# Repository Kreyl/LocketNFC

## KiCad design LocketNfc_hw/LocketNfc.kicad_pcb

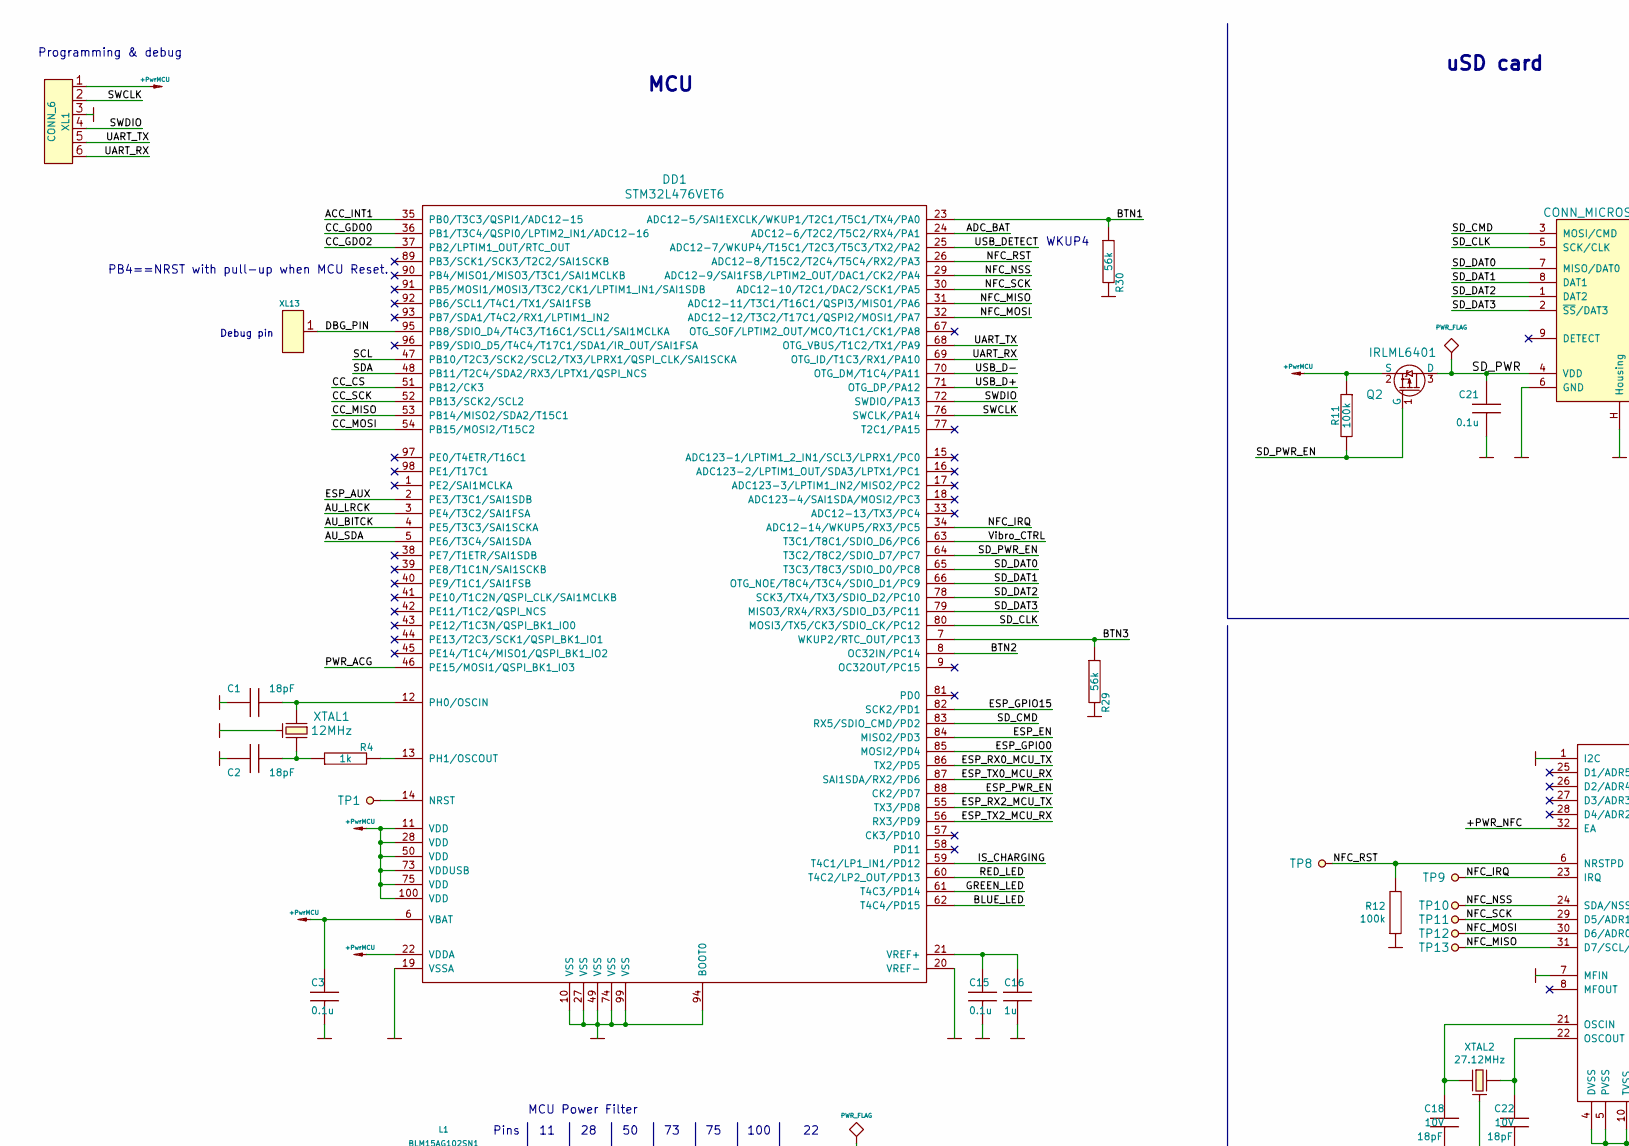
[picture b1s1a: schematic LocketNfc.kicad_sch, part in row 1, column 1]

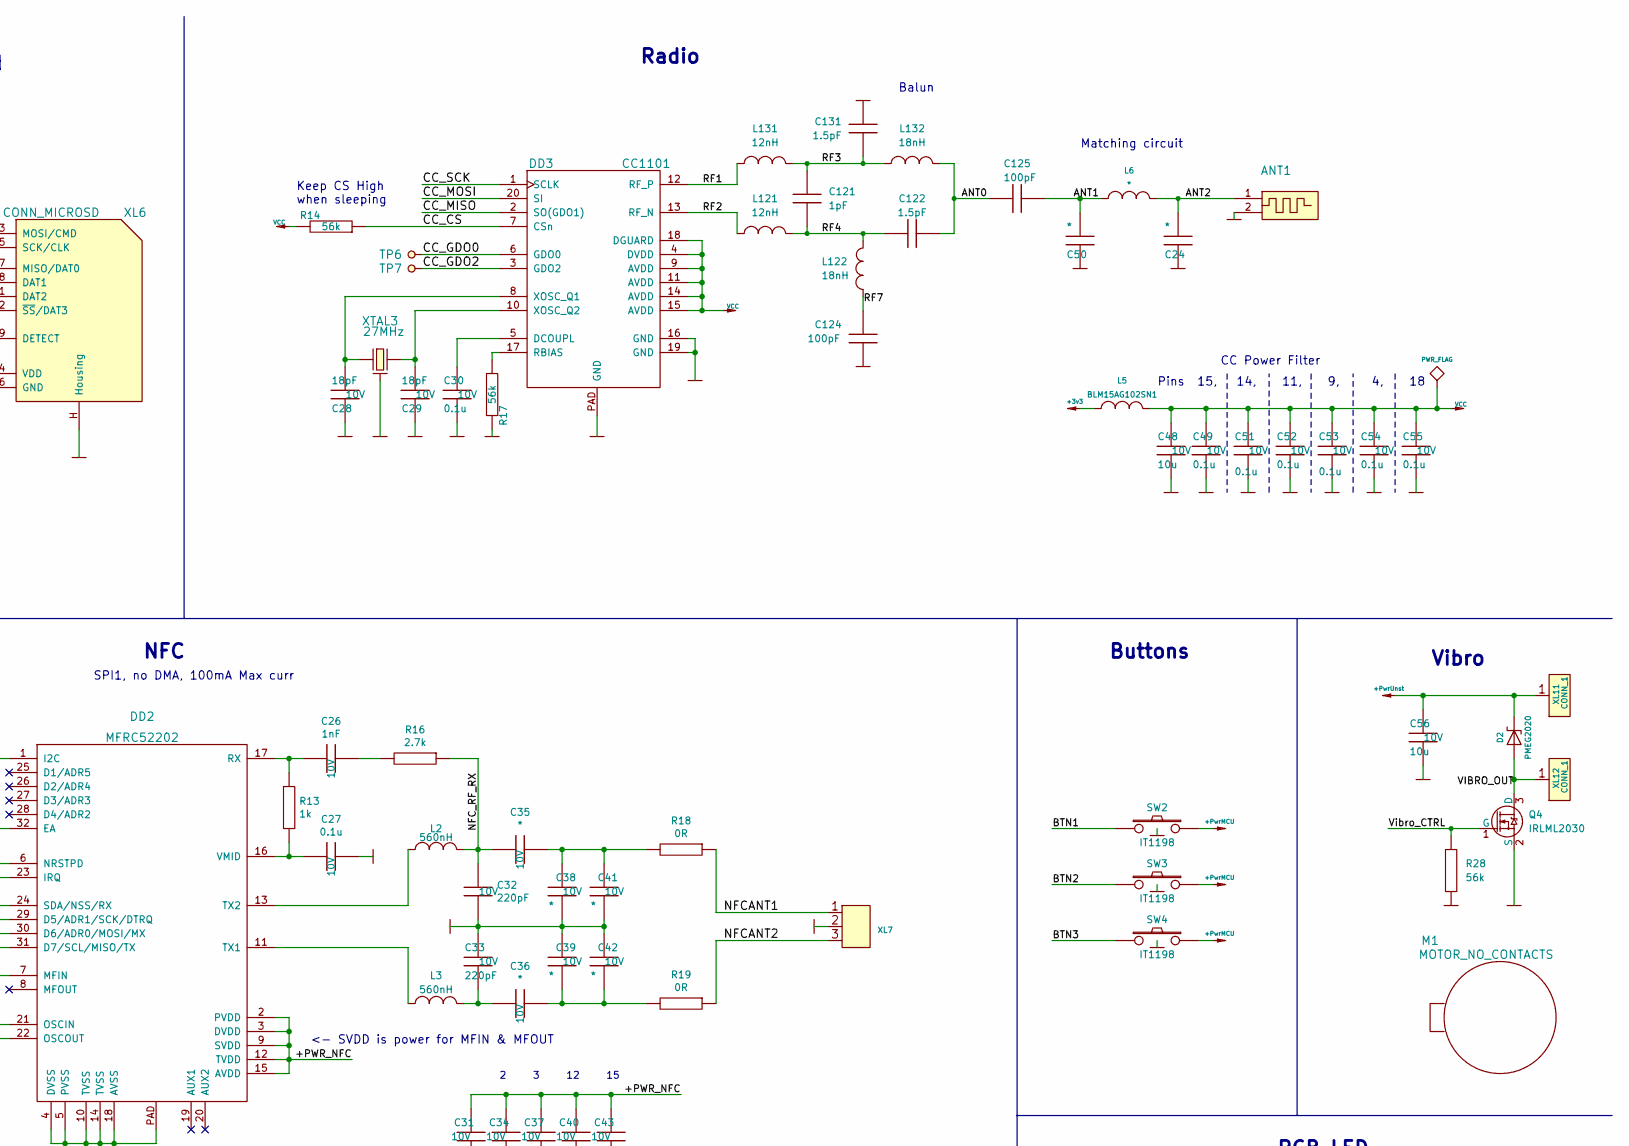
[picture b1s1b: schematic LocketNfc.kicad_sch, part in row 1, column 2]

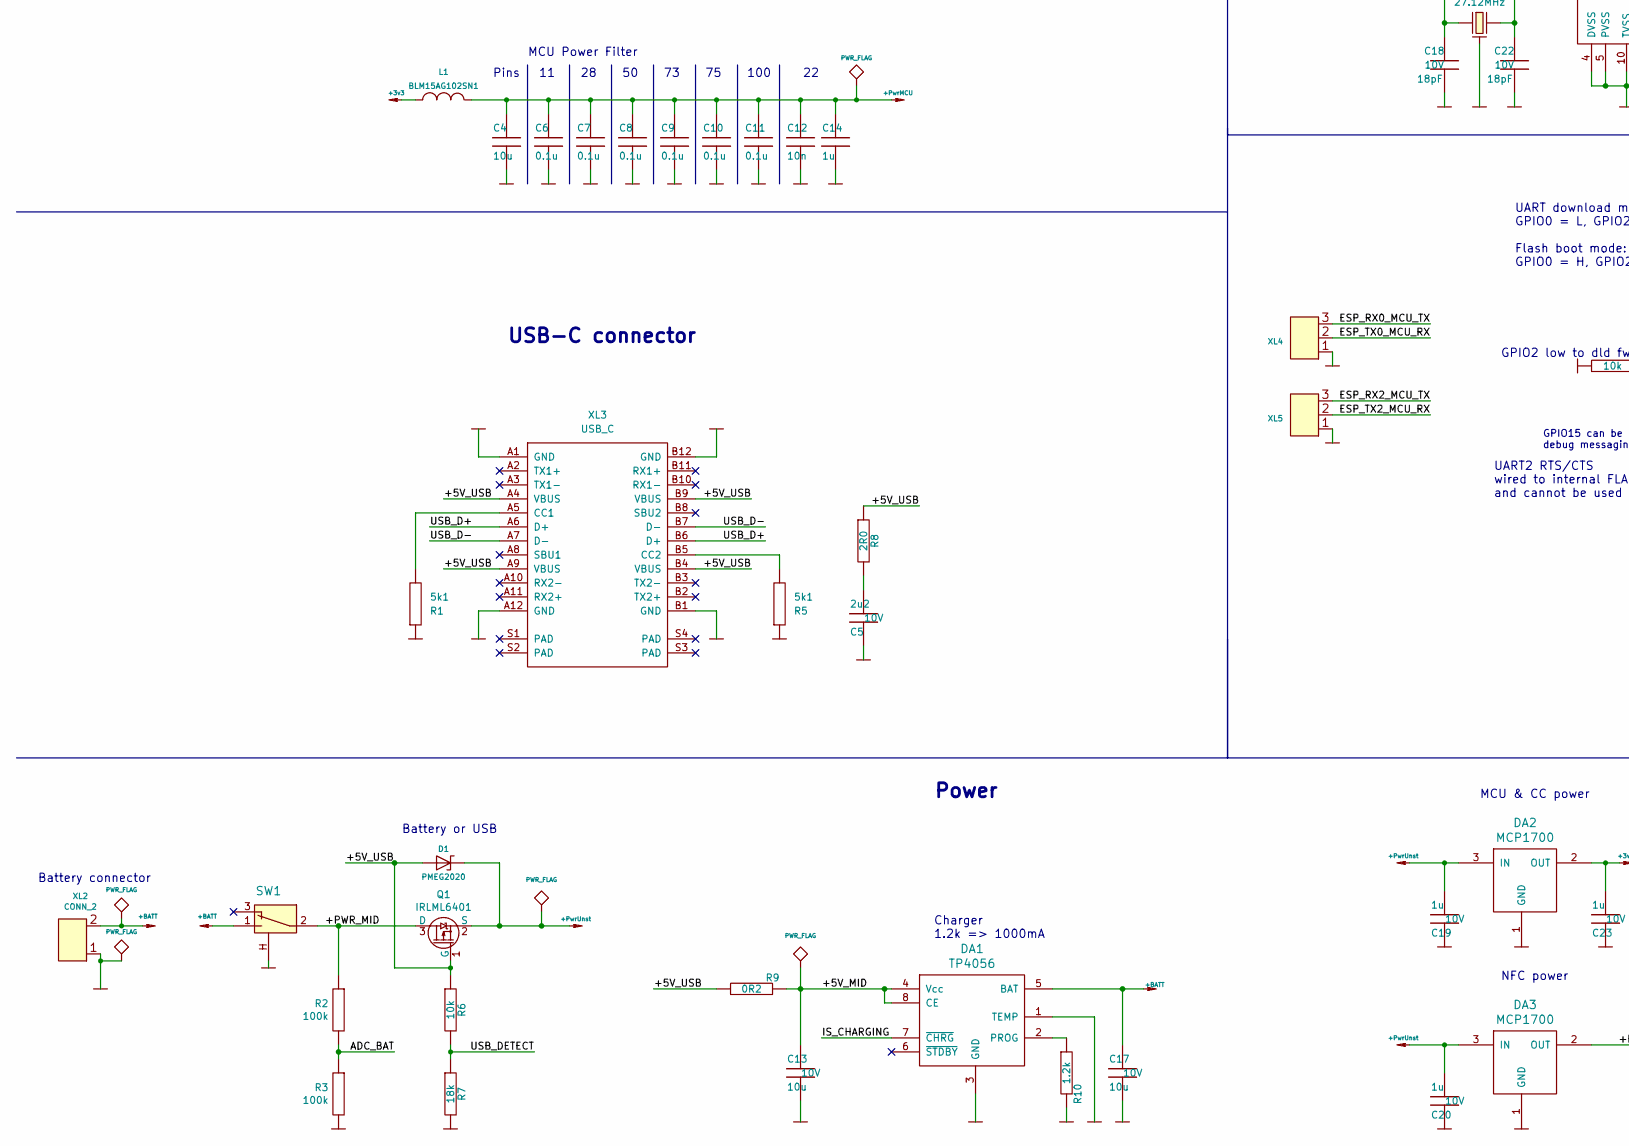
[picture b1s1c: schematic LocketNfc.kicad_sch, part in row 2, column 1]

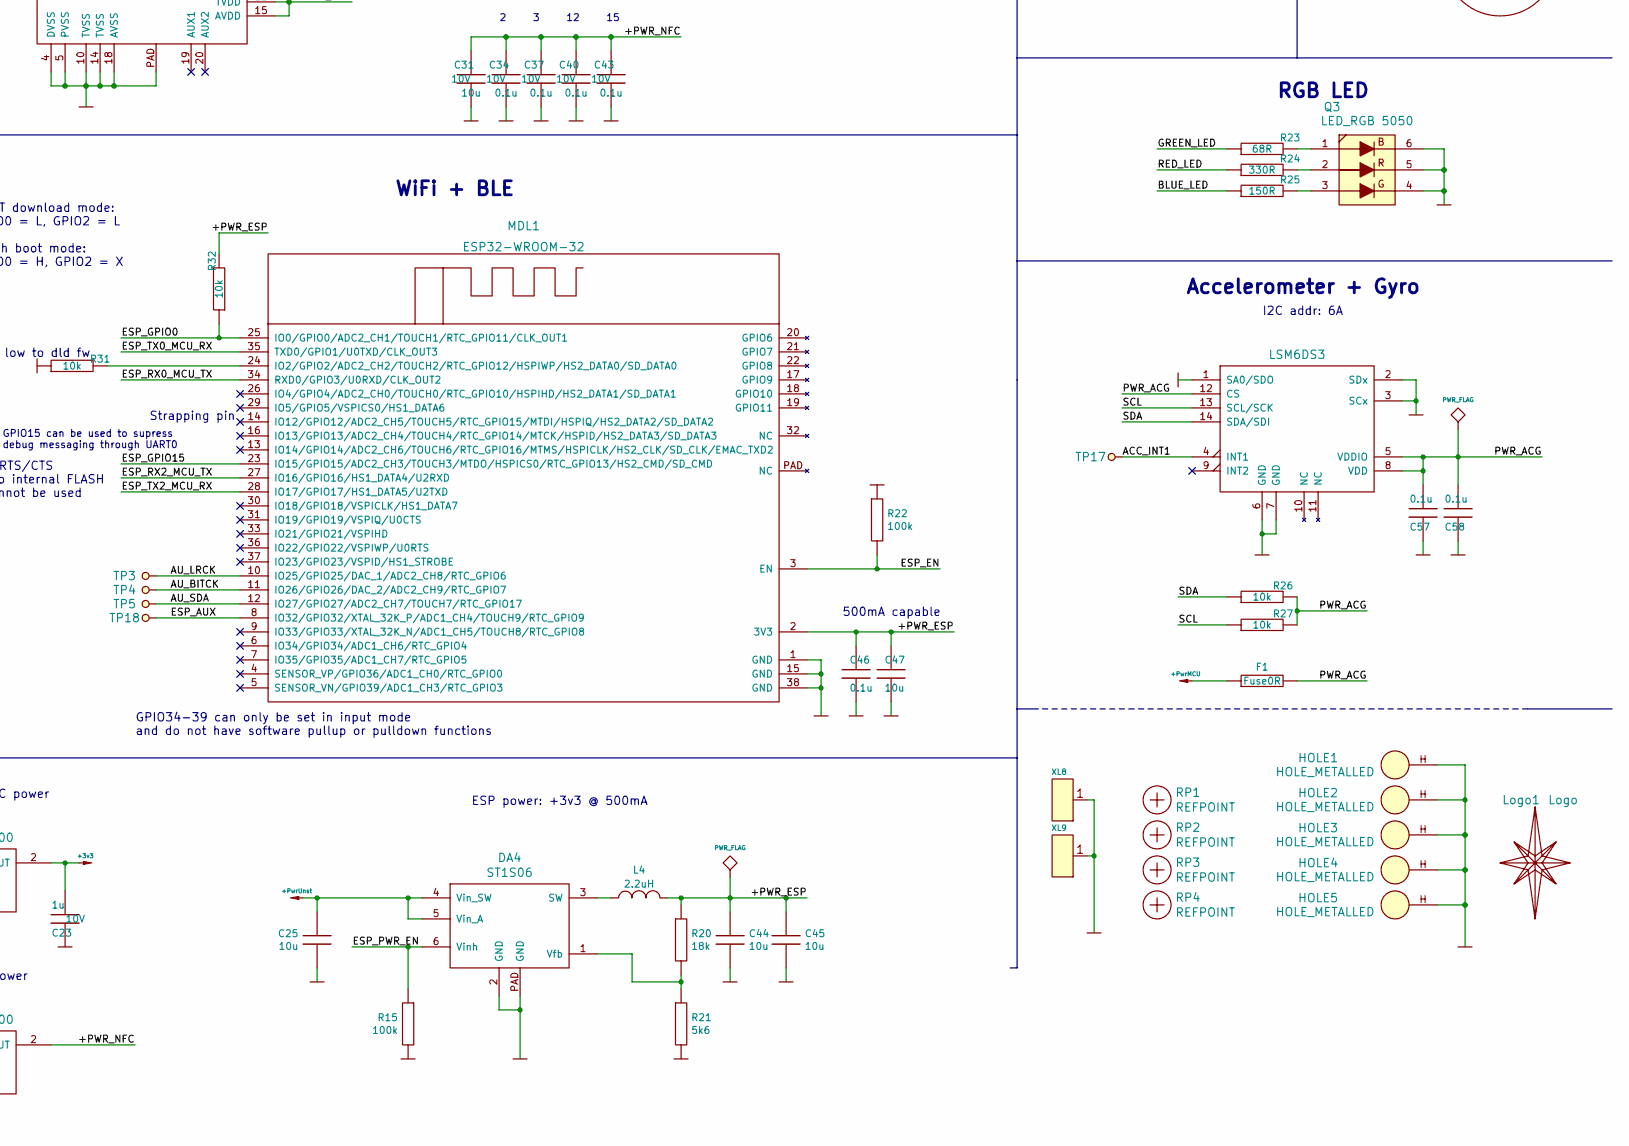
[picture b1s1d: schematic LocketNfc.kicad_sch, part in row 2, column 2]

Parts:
ANT1: ANT_PCB_MONO_2PIN; LocketNFC_inverted
C1, C2: 18pF; CAP_0603_Silks
C3, C6, C7, C8, C9, C10, C11, C15, C21, C46, C57, C58: 0.1u; CAP_0603_Silks
C4, C25, C44, C45, C47: 10u; CAP_0603_Silks
C5: 2u2; CAP_0603_Silks; Tolerance 20%; Voltage 10V
C12: 10n; CAP_0603_Silks
C13, C17, C31, C48, C56: 10u; CAP_0603_Silks; Tolerance 20%; Voltage 10V
C14, C16: 1u; CAP_0603_Silks
C18, C22, C28, C29: 18pF; CAP_0603_Silks; Tolerance 20%; Voltage 10V
C19, C20, C23: 1u; CAP_0603_Silks; Tolerance 20%; Voltage 10V
C24, C50: *; CAP_0402; Tolerance 20%; Voltage 10V
C26: 1nF; CAP_0603_Silks; Tolerance 20%; Voltage 10V
C27, C30, C34, C37, C40, C43, C49, C51, C52, C53, C54, C55: 0.1u; CAP_0603_Silks; Tolerance 20%; Voltage 10V
C32, C33: 220pF; CAP_0603_Silks; Tolerance 20%; Voltage 10V
C35, C36, C38, C39, C41, C42: *; CAP_0603_Silks; Tolerance 20%; Voltage 10V
C121: 1pF; CAP_0402; Tolerance 20%; Voltage 10V
C122, C131: 1.5pF; CAP_0402; Tolerance 20%; Voltage 10V
C124, C125: 100pF; CAP_0402; Tolerance 20%; Voltage 10V
D1, D2: PMEG2020; SOD323
DA1: TP4056; SO8_150MIL
DA2, DA3: MCP1700; SOT23-3
DA4: ST1S06; DFN6_3x3
DD1: STM32L476VET6; LQFP100
DD2: MFRC52202; QFN32_EP_5x5_Pitch0.5mm
DD3: CC1101; QFN20
DD4: LSM6DS3; 14_3x2d5_p0d5
F1: Fuse0R; RES_0603_FUSE
HOLE1, HOLE2, HOLE3, HOLE4, HOLE5: HOLE_METALLED; Hole2d2_out3d5mm
L1, L5: BLM15AG102SN1; IND_0402; Tolerance 20%
L2, L3: 560nH; IND_0805; Tolerance 20%
L4: 2.2uH; IND_SRN2512
L6: *; IND_0402; Tolerance 20%
L121, L131: 12nH; IND_0402; Tolerance 20%
L122, L132: 18nH; IND_0402; Tolerance 20%
Logo1: Logo; Ostranna_12d7_10d1
M1: MOTOR_NO_CONTACTS; Motor_no_Contacts
MDL1: ESP32-WROOM-32; ESP32WROOM32
Q1, Q2: IRLML6401; SOT23-3
Q3: LED_RGB 5050; LED_5050
Q4: IRLML2030; SOT23-3
R1, R5: 5k1; RES_0603; Tolerance 1%
R2, R3, R11, R15, R22: 100k; RES_0603
R4: 1k; RES_0603
R6: 10k; RES_0603; Tolerance 1%
R7: 18k; RES_0603; Tolerance 1%
R8: 2R0; RES_0603; Tolerance 1%
R9: 0R2; RES_1206; Tolerance 1%
R10: 1.2k; RES_0603; Tolerance 1%
R12: 100k; RES_0603; Tolerance 1%
R13: 1k; RES_0603; Tolerance 1%
R14, R17, R28, R29, R30: 56k; RES_0603; Tolerance 1%
R16: 2.7k; RES_0603; Tolerance 1%
R18, R19: 0R; RES_0603; Tolerance 1%
R20: 18k; RES_0603
R21: 5k6; RES_0603
R23: 68R; RES_0603; Tolerance 1%
R24: 330R; RES_0603; Tolerance 1%
R25: 150R; RES_0603; Tolerance 1%
R26, R27, R31, R32: 10k; RES_0603
RP1, RP2, RP3, RP4: REFPOINT; REF_POINT_1MM
SW1: SWITCH; SW_SS-1P2T_Housing
SW2, SW3, SW4: IT1198; BTN_IT1198
TP1, TP3, TP4, TP5, TP6, TP7, TP8, TP9, TP10, TP11, TP12, TP13, TP17, TP18: TESTPOINT; TESTPOINT_1MM
XL1: CONN_6; PLS-6_LOCK
XL2: CONN_2; SLD_2_2D5
XL3: USB_C; USB_C_MOLEX_1054500101
XL4, XL5, XL7: CONN_3; PLS-3
XL6: CONN_MICROSD; MICROSD_EJECTOR_TFWF1
XL8, XL9: CONN_1; PLS-1Square
XL11, XL12: CONN_1; Oval3x1.5
XL13: CONN_1; PLS-1Rnd
XTAL1: 12MHz; 03225C4
XTAL2: 27.12MHz; 0503x4-4
XTAL3: 27MHz; 03225C4

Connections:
+3v3: C23.1, DA2.2 (OUT), L1.2, L5.2
+BATT: C17.2, DA1.5 (BAT), SW1.1, XL2.2 (PM)
+PwrMCU: C3.2, C4.2, C6.2, C7.2, C8.2, C9.2, C10.2, C11.2, C12.2, C14.2, DD1.6 (VBAT), DD1.11 (VDD), DD1.22 (VDDA), DD1.28 (VDD), DD1.50 (VDD), DD1.73 (VDDUSB), DD1.75 (VDD), DD1.100 (VDD), F1.1, L1.1, Q2.2 (S), R11.1, SW2.2, SW3.2, SW4.2, XL1.1
+PwrUnst: C19.1, C20.1, C25.1, C56.2, D1.C, D2.C, DA2.3 (IN), DA3.3 (IN), DA4.4 (Vin_SW), DA4.5 (Vin_A), Q1.2 (S), XL11.1
/+5V_MID: C13.2, DA1.4 (Vcc), DA1.8 (CE), R9.2
/+5V_USB: D1.A, Q1.1 (G), R6.1, R8.1, R9.1, XL3.A4 (VBUS), XL3.A9 (VBUS), XL3.B4 (VBUS), XL3.B9 (VBUS)
/+PWR_ESP: C44.1, C45.1, C46.1, C47.1, L4.2, MDL1.2 (3V3), R20.1, R32.2
/+PWR_MID: Q1.3 (D), R2.1, SW1.2
/+PWR_NFC: C31.2, C34.2, C37.2, C40.2, C43.2, DA3.2 (OUT), DD2.2 (PVDD), DD2.3 (DVDD), DD2.9 (SVDD), DD2.12 (TVDD), DD2.15 (AVDD), DD2.32 (EA)
/ACC_INT1: DD1.35 (PB0/T3C3/QSPI1/ADC12-15), DD4.4 (INT1), TP17.1
/ADC_BAT: DD1.24 (ADC12-6/T2C2/T5C2/RX4/PA1), R2.2, R3.1
/ANT0: C122.2, C125.2, L132.1
/ANT1: C50.1, C125.1, L6.2
/ANT2: ANT1.1, C24.1, L6.1
/AU_BITCK: DD1.4 (PE5/T3C3/SAI1SCKA), MDL1.11 (IO26/GPIO26/DAC_2/ADC2_CH9/RTC_GPIO7), TP4.1
/AU_LRCK: DD1.3 (PE4/T3C2/SAI1FSA), MDL1.10 (IO25/GPIO25/DAC_1/ADC2_CH8/RTC_GPIO6), TP3.1
/AU_SDA: DD1.5 (PE6/T3C4/SAI1SDA), MDL1.12 (IO27/GPIO27/ADC2_CH7/TOUCH7/RTC_GPIO17), TP5.1
/BLUE_LED: DD1.62 (T4C4/PD15), R25.1
/BTN1: DD1.23 (ADC12-5/SAI1EXCLK/WKUP1/T2C1/T5C1/TX4/P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), R30.1, SW2.1
/BTN2: DD1.8 (OC32IN/PC14), SW3.1
/BTN3: DD1.7 (WKUP2/RTC_OUT/PC13), R29.1, SW4.1
/CC_CS: DD1.51 (PB12/CK3), DD3.7 (CSn), R14.1
/CC_GDO0: DD1.36 (PB1/T3C4/QSPI0/LPTIM2_IN1/ADC12-16), DD3.6 (GDO0), TP6.1
/CC_GDO2: DD1.37 (PB2/LPTIM1_OUT/RTC_OUT), DD3.3 (GDO2), TP7.1
/CC_MISO: DD1.53 (PB14/MISO2/SDA2/T15C1), DD3.2 (SO(GDO1))
/CC_MOSI: DD1.54 (PB15/MOSI2/T15C2), DD3.20 (SI)
/CC_SCK: DD1.52 (PB13/SCK2/SCL2), DD3.1 (SCLK)
/DBG_PIN: DD1.95 (PB8/SDIO_D4/T4C3/T16C1/SCL1/SAI1MCLKA), XL13.1
/ESP_AUX: DD1.2 (PE3/T3C1/SAI1SDB), MDL1.8 (IO32/GPIO32/XTAL_32K_P/ADC1_CH4/TOUCH9/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), TP18.1
/ESP_EN: DD1.84 (MISO2/PD3), MDL1.3 (EN), R22.2
/ESP_GPIO0: DD1.85 (MOSI2/PD4), MDL1.25 (IO0/GPIO0/ADC2_CH1/TOUCH1/RTC_GPIO11/CL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), R32.1
/ESP_GPIO15: DD1.82 (SCK2/PD1), MDL1.23 (IO15/GPIO15/ADC2_CH3/TOUCH3/MTDO/HSPICS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)
/ESP_PWR_EN: DA4.6 (Vinh), DD1.88 (CK2/PD7), R15.1
/ESP_RX0_MCU_TX: DD1.86 (TX2/PD5), MDL1.34 (RXD0/GPIO3/U0RXD/CLK_OUT2), XL4.3
/ESP_RX2_MCU_TX: DD1.55 (TX3/PD8), MDL1.27 (IO16/GPIO16/HS1_DATA4/U2RXD), XL5.3
/ESP_TX0_MCU_RX: DD1.87 (SAI1SDA/RX2/PD6), MDL1.35 (TXD0/GPIO1/U0TXD/CLK_OUT3), XL4.2 (PM)
/ESP_TX2_MCU_RX: DD1.56 (RX3/PD9), MDL1.28 (IO17/GPIO17/HS1_DATA5/U2TXD), XL5.2 (PM)
/GREEN_LED: DD1.61 (T4C3/PD14), R23.1
/IS_CHARGING: DA1.7 (~CHRG), DD1.59 (T4C1/LP1_IN1/PD12)
/NFCANT1: R18.1, XL7.1
/NFCANT2: R19.1, XL7.3
/NFC_IRQ: DD1.34 (ADC12-14/WKUP5/RX3/PC5), DD2.23 (IRQ), TP9.1
/NFC_MISO: DD1.31 (ADC12-11/T3C1/T16C1/QSPI3/MISO1/PA6), DD2.31 (D7/SCL/MISO/TX), TP13.1
/NFC_MOSI: DD1.32 (ADC12-12/T3C2/T17C1/QSPI2/MOSI1/PA7), DD2.30 (D6/ADR0/MOSI/MX), TP12.1
/NFC_NSS: DD1.29 (ADC12-9/SAI1FSB/LPTIM2_OUT/DAC1/CK2/PA4), DD2.24 (SDA/NSS/RX), TP10.1
/NFC_RF_RX: C32.1, C35.2, L2.1, R16.1
/NFC_RST: DD1.26 (ADC12-8/T15C2/T2C4/T5C4/RX2/PA3), DD2.6 (NRSTPD), R12.2, TP8.1
/NFC_SCK: DD1.30 (ADC12-10/T2C1/DAC2/SCK1/PA5), DD2.29 (D5/ADR1/SCK/DTRQ), TP11.1
/PWR_ACG: C57.1, C58.1, DD1.46 (PE15/MOSI1/QSPI_BK1_IO3), DD4.5 (VDDIO), DD4.8 (VDD), DD4.12 (CS), F1.2, R26.2, R27.2
/RED_LED: DD1.60 (T4C2/LP2_OUT/PD13), R24.1
/RF1: DD3.12 (RF_P), L131.2
/RF2: DD3.13 (RF_N), L121.2
/RF3: C121.1, C131.1, L131.1, L132.2
/RF4: C121.2, C122.1, L121.1, L122.1
/RF7: C124.2, L122.2
/SCL: DD1.47 (PB10/T2C3/SCK2/SCL2/TX3/LPRX1/QSPI_CLK/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), DD4.13 (SCL/SCK), R27.1
/SDA: DD1.48 (PB11/T2C4/SDA2/RX3/LPTX1/QSPI_NCS), DD4.14 (SDA/SDI), R26.1
/SD_CLK: DD1.80 (MOSI3/TX5/CK3/SDIO_CK/PC12), XL6.5 (SCK/CLK)
/SD_CMD: DD1.83 (RX5/SDIO_CMD/PD2), XL6.3 (MOSI/CMD)
/SD_DAT0: DD1.65 (T3C3/T8C3/SDIO_D0/PC8), XL6.7 (MISO/DAT0)
/SD_DAT1: DD1.66 (OTG_NOE/T8C4/T3C4/SDIO_D1/PC9), XL6.8 (DAT1)
/SD_DAT2: DD1.78 (SCK3/TX4/TX3/SDIO_D2/PC10), XL6.1 (DAT2)
/SD_DAT3: DD1.79 (MISO3/RX4/RX3/SDIO_D3/PC11), XL6.2 (~SS/DAT3)
/SD_PWR: C21.1, Q2.3 (D), XL6.4 (VDD)
/SD_PWR_EN: DD1.64 (T3C2/T8C2/SDIO_D7/PC7), Q2.1 (G), R11.2
/SWCLK: DD1.76 (SWCLK/PA14), XL1.2
/SWDIO: DD1.72 (SWDIO/PA13), XL1.4
/UART_RX: DD1.69 (OTG_ID/T1C3/RX1/PA10), XL1.6
/UART_TX: DD1.68 (OTG_VBUS/T1C2/TX1/PA9), XL1.5
/USB_D+: DD1.71 (OTG_DP/PA12), XL3.A6 (D+), XL3.B6 (D+)
/USB_D-: DD1.70 (OTG_DM/T1C4/PA11), XL3.A7 (D-), XL3.B7 (D-)
/USB_DETECT: DD1.25 (ADC12-7/WKUP4/T15C1/T2C3/T5C3/TX2/PA2), R6.2, R7.1
/VIBRO_OUT: D2.A, Q4.3 (D), XL12.1
/Vibro_CTRL: DD1.63 (T3C1/T8C1/SDIO_D6/PC6), Q4.1 (G), R28.1
GND: ANT1.2, C1.2, C2.2, C3.1, C4.1, C5.2, C6.1, C7.1, C8.1, C9.1, C10.1, C11.1, C12.1, C13.1, C14.1, C15.1, C16.1, C17.1, C18.2, C19.2, C20.2, C21.2, C22.2, C23.2, C24.2, C25.2, C27.1, C28.2, C29.2, C30.1, C31.1, C32.2, C33.1, C34.1, C37.1, C38.2, C39.1, C40.1, C41.2, C42.1, C43.1, C44.2, C45.2, C46.2, C47.2, C48.2, C49.2, C50.2, C51.2, C52.2, C53.2, C54.2, C55.2, C56.1, C57.2, C58.2, C124.1, C131.2, DA1.1 (TEMP), DA1.3 (GND), DA2.1 (GND), DA3.1 (GND), DA4.2 (GND), DA4.PAD (GND), DD1.10 (VSS), DD1.19 (VSSA), DD1.20 (VREF-), DD1.27 (VSS), DD1.49 (VSS), DD1.74 (VSS), DD1.94 (BOOT0), DD1.99 (VSS), DD2.1 (I2C), DD2.4 (DVSS), DD2.5 (PVSS), DD2.7 (MFIN), DD2.10 (TVSS), DD2.14 (TVSS), DD2.18 (AVSS), DD2.PAD, DD3.16 (GND), DD3.19 (GND), DD3.PAD (GND), DD4.1 (SA0/SDO), DD4.2 (SDx), DD4.3 (SCx), DD4.6 (GND), DD4.7 (GND), HOLE1.H, HOLE2.H, HOLE3.H, HOLE4.H, HOLE5.H, MDL1.1 (GND), MDL1.15 (GND), MDL1.38 (GND), Q3.4 (B), Q3.5 (G), Q3.6, Q4.2 (S), R1.1, R3.2, R5.1, R7.2, R10.2, R12.1, R15.2, R17.2, R21.2, R22.1, R28.2, R29.2, R30.2, R31.1, SW1.H, SW2.H, SW3.H, SW4.H, XL1.3, XL2.1, XL3.A1 (GND), XL3.A12 (GND), XL3.B1 (GND), XL3.B12 (GND), XL4.1, XL5.1, XL6.6 (GND), XL6.H (Housing), XL7.2 (PM), XL8.1, XL9.1, XTAL1.H, XTAL2.H, XTAL3.H
unnamed: C1.1, DD1.12 (PH0/OSCIN), XTAL1.1
unnamed: C2.1, R4.1, XTAL1.2
unnamed: C5.1, R8.2
unnamed: C15.2, C16.2, DD1.21 (VREF+)
unnamed: C18.1, DD2.21 (OSCIN), XTAL2.1
unnamed: C22.1, DD2.22 (OSCOUT), XTAL2.2
unnamed: C26.1, R16.2
unnamed: C26.2, DD2.17 (RX), R13.1
unnamed: C27.2, DD2.16 (VMID), R13.2
unnamed: C28.1, DD3.8 (XOSC_Q1), XTAL3.1
unnamed: C29.1, DD3.10 (XOSC_Q2), XTAL3.2
unnamed: C30.2, DD3.5 (DCOUPL)
unnamed: C33.2, C36.2, L3.1
unnamed: C35.1, C38.1, C41.1, R18.2
unnamed: C36.1, C39.2, C42.2, R19.2
unnamed: DA1.2 (PROG), R10.1
unnamed: DA4.1 (Vfb), R20.2, R21.1
unnamed: DA4.3 (SW), L4.1
unnamed: DD1.13 (PH1/OSCOUT), R4.2
unnamed: DD1.14 (NRST), TP1.1
unnamed: DD2.11 (TX1), L3.2
unnamed: DD2.13 (TX2), L2.2
unnamed: DD3.17 (RBIAS), R17.1
unnamed: MDL1.24 (IO2/GPIO2/ADC2_CH2/TOUCH2/RTC_GPIO12/HS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), R31.2
unnamed: Q3.1, R23.2
unnamed: Q3.2, R24.2
unnamed: Q3.3, R25.2
unnamed: R1.2, XL3.A5 (CC1)
unnamed: R5.2, XL3.B5 (CC2)
VCC: C48.1, C49.1, C51.1, C52.1, C53.1, C54.1, C55.1, DD3.4 (DVDD), DD3.9 (AVDD), DD3.11 (AVDD), DD3.14 (AVDD), DD3.15 (AVDD), DD3.18 (DGUARD), L5.1, R14.2

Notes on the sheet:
I2C addr: 6A
500mA capable
CC Power Filter
Charger 1.2k => 1000mA
UART download mode: GPIO0 = L, GPIO2 = L Flash boot mode: GPIO0 = H, GPIO2 = X
Strapping pin
WiFi + BLE
uSD card
MCU
2 3 12 15
Radio
Power
NFC power
WKUP4
Programming & debug
GPIO2 low to dld fw
Keep CS High when sleeping
Battery connector
Battery or USB
GPIO34-39 can only be set in input mode and do not have software pullup or pulldown functions
PB4==NRST with pull-up when MCU Reset.
RGB LED
NFC
Matching circuit
MCU Power Filter
UART2 RTS/CTS wired to internal FLASH and cannot be used
SPI1, no DMA, 100mA Max curr
USB-C connector
Debug pin
GPIO15 can be used to supress debug messaging through UART0
MCU & CC power
Pins 11 28 50 73 75 100 22
<- SVDD is power for MFIN & MFOUT
Balun
Vibro
Buttons
Pins 15, 14, 11, 9, 4, 18
Accelerometer + Gyro
ESP power: +3v3 @ 500mA

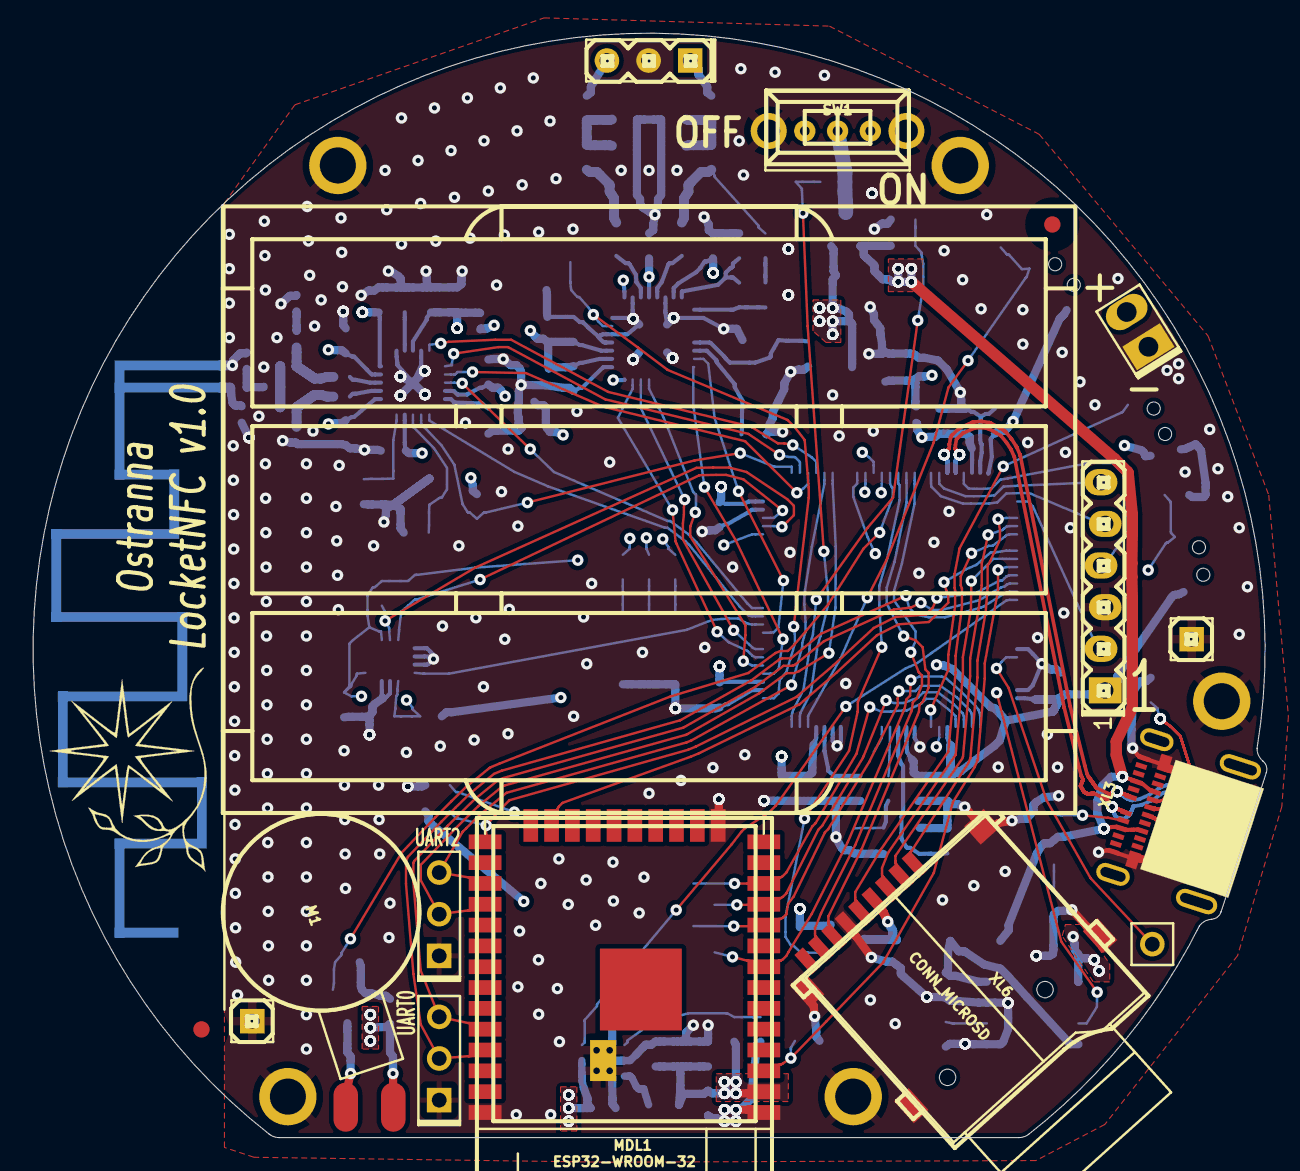
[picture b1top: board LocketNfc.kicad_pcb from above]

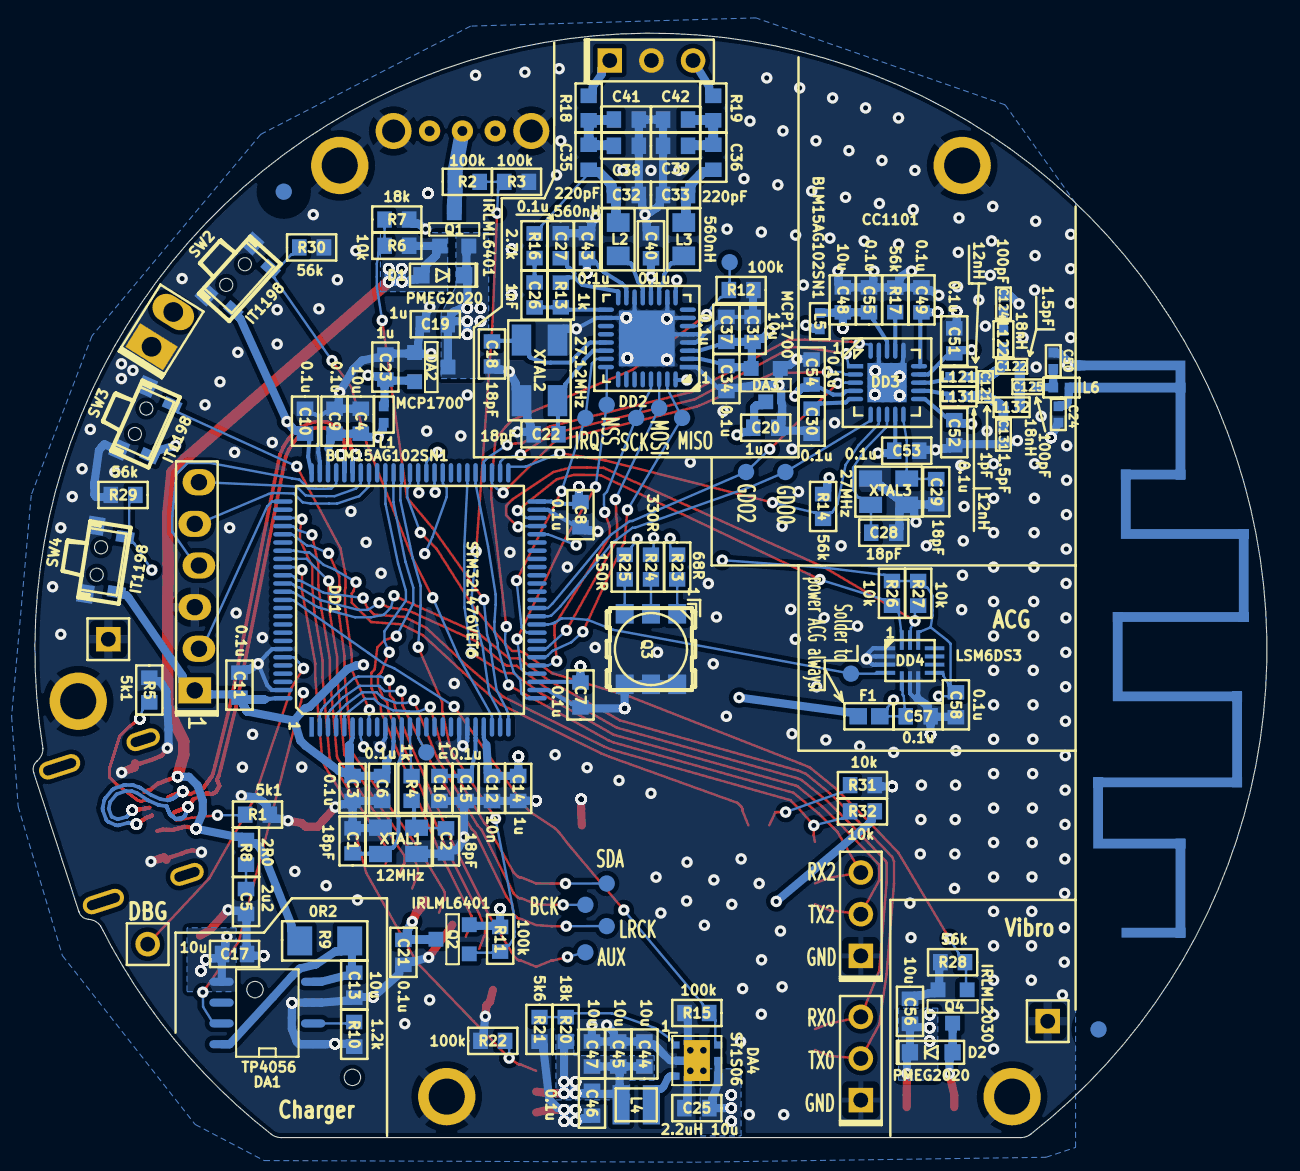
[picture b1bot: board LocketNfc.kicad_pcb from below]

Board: 4 copper layers, 75.2 x 67.4 mm, 166 parts (145 on the bottom side), 105 nets.

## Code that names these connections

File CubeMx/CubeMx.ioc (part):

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Mcu.Name=STM32L476V(C-E-G)Tx
Mcu.Package=LQFP100
Mcu.UserName=STM32L476VETx
PA0.Mode=SYS_WakeUp0
PA0.Signal=SYS_WKUP1
PA1.Signal=GPIO_Output
PA10.Mode=Asynchronous
PA10.Signal=USART1_RX
PA11.Mode=Device_Only
PA11.Signal=USB_OTG_FS_DM
PA12.Mode=Device_Only
PA12.Signal=USB_OTG_FS_DP
PA13\ (JTMS-SWDIO).Mode=Serial_Wire
PA13\ (JTMS-SWDIO).Signal=SYS_JTMS-SWDIO
PA14\ (JTCK-SWCLK).Mode=Serial_Wire
PA14\ (JTCK-SWCLK).Signal=SYS_JTCK-SWCLK
PA15\ (JTDI).Signal=GPIO_Analog
PA2.Mode=SYS_WakeUp3
PA2.Signal=SYS_WKUP4
PA3.Signal=GPIO_Input
PA4.Signal=GPIO_Output
PA5.Mode=Full_Duplex_Master
PA5.Signal=SPI1_SCK
PA6.Mode=Full_Duplex_Master
PA6.Signal=SPI1_MISO
PA7.Mode=Full_Duplex_Master
PA7.Signal=SPI1_MOSI
PA8.Mode=Clock-out
PA8.Signal=RCC_MCO
PA9.Mode=Asynchronous
PA9.Signal=USART1_TX
PB10.Mode=I2C
PB10.Signal=I2C2_SCL
PB11.Mode=I2C
PB11.Signal=I2C2_SDA
PB12.Signal=GPIO_Output
PB13.Mode=Full_Duplex_Master
PB13.Signal=SPI2_SCK
PB14.Mode=Full_Duplex_Master
PB14.Signal=SPI2_MISO
PB15.Mode=Full_Duplex_Master
PB15.Signal=SPI2_MOSI
PB3\ (JTDO-TRACESWO).Signal=GPXTI3
PB4\ (NJTRST).Signal=GPIO_Analog
PC10.Mode=SD_4_bits_Wide_bus
PC10.Signal=SDMMC1_D2
PC11.Mode=SD_4_bits_Wide_bus
PC11.Signal=SDMMC1_D3
PC12.Mode=SD_4_bits_Wide_bus
PC12.Signal=SDMMC1_CK
PC13.Mode=SYS_WakeUp1
PC13.Signal=SYS_WKUP2
PC2.Signal=GPIO_Input
PC3.Mode=SAI_A_MasterWithClock
PC3.Signal=SAI1_SD_A
PC5.Mode=SYS_WakeUp4
PC5.Signal=SYS_WKUP5
PC6.Signal=S_TIM3_CH1
PC8.Mode=SD_4_bits_Wide_bus
PC8.Signal=SDMMC1_D0
PC9.Mode=SD_4_bits_Wide_bus
PC9.Signal=SDMMC1_D1
PD13.Signal=S_TIM4_CH2
PD14.Signal=S_TIM4_CH3
PD15.Signal=S_TIM4_CH4
PD2.Mode=SD_4_bits_Wide_bus
PD2.Signal=SDMMC1_CMD
PD5.Mode=Asynchronous
PD5.Signal=USART2_TX
PD6.Mode=Asynchronous
PD6.Signal=USART2_RX
PD8.Mode=Asynchronous
PD8.Signal=USART3_TX
PD9.Mode=Asynchronous
PD9.Signal=USART3_RX
PE15.Signal=GPIO_Output
PE2.Mode=SAI_A_MasterWithClock
PE2.Signal=SAI1_MCLK_A
PE4.Mode=SAI_A_MasterWithClock
PE4.Signal=SAI1_FS_A
PE5.Mode=SAI_A_MasterWithClock
PE5.Signal=SAI1_SCK_A
PE6.Mode=SYS_WakeUp2
PE6.Signal=SYS_WKUP3
PH0-OSC_IN\ (PH0).Mode=HSE-External-Oscillator
PH0-OSC_IN\ (PH0).Signal=RCC_OSC_IN
PH1-OSC_OUT\ (PH1).Mode=HSE-External-Oscillator
PH1-OSC_OUT\ (PH1).Signal=RCC_OSC_OUT
RCC.HSE_VALUE=12000000
board=custom

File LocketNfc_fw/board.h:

/*
 * board.h
 *
 *  Created on: 05 08 2018
 *      Author: Kreyl
 */

#pragma once

// ==== General ====
#define APP_NAME            "LocketNFC"

// Version of PCB
#define PCB_VER                 1

// MCU type as defined in the ST header.
#define STM32L476xx

// Freq of external crystal if any. Leave it here even if not used.
#define CRYSTAL_FREQ_HZ         12000000

// OS timer settings
#define STM32_ST_IRQ_PRIORITY   2
#define STM32_ST_USE_TIMER      5
#define STM32_TIMCLK1           (Clk.APB1FreqHz)    // Timer 5 is clocked by APB1

//  Periphery
#define I2C1_ENABLED            FALSE
#define I2C2_ENABLED            TRUE
#define I2C3_ENABLED            FALSE

#define ADC_REQUIRED            FALSE
#define STM32_DMA_REQUIRED      TRUE    // Leave this macro name for OS

#if 1 // ========================== GPIO =======================================
// EXTI
#define INDIVIDUAL_EXTI_IRQ_REQUIRED    FALSE

// Buttons
#define BTN1_PIN        GPIOA, 0, pudPullDown
#define BTN2_PIN        GPIOC, 14, pudPullDown
#define BTN3_PIN        GPIOC, 13, pudPullDown

// Charging
#define IS_CHARGING_PIN GPIOD, 12

// UART
#define UART_TX_PIN     GPIOA, 9
#define UART_RX_PIN     GPIOA, 10

// USB
#define USB_DM          GPIOA, 11
#define USB_DP          GPIOA, 12
#define USB_AF          AF10
// USB detect
#define USB_DETECT_PIN  GPIOA, 2

// MFRC52202
#define NFC_RST         GPIOA, 3
#define NFC_IRQ         GPIOC, 5
#define NFC_NSS         GPIOA, 4
#define NFC_SCK         GPIOA, 5
#define NFC_MOSI        GPIOA, 7
#define NFC_MISO        GPIOA, 6

// Vibro
#define VIBRO_SETUP     { GPIOC, 6, TIM3, 1, invNotInverted, omPushPull, 99 }

// SD
#define SD_PWR_PIN      GPIOC, 7
#define SD_AF           AF12
#define SD_DAT0         GPIOC,  8, omPushPull, pudPullUp, SD_AF
#define SD_DAT1         GPIOC,  9, omPushPull, pudPullUp, SD_AF
#define SD_DAT2         GPIOC, 10, omPushPull, pudPullUp, SD_AF
#define SD_DAT3         GPIOC, 11, omPushPull, pudPullUp, SD_AF
#define SD_CLK          GPIOC, 12, omPushPull, pudNone,   SD_AF
#define SD_CMD          GPIOD,  2, omPushPull, pudPullUp, SD_AF

// ESP32
#define ESP_GPIO15      GPIOD, 1
#define ESP_EN          GPIOD, 3
#define ESP_PWR_EN      GPIOD, 7
#define ESP_GPIO0       GPIOD, 4
#define ESP_AUX         GPIOE, 3
#define ESP_TX0         GPIOD, 6
#define ESP_RX0         GPIOD, 5
#define ESP_RX2_MCU_TX  GPIOD, 8
#define ESP_TX2_MCU_RX  GPIOD, 9
// Audio
#define AU_LRCK         GPIOE, 4, omPushPull, pudNone, AF13
#define AU_SCLK         GPIOE, 5, omPushPull, pudNone, AF13
#define AU_SDIN         GPIOE, 6, omPushPull, pudNone, AF13 // MOSI; SAI1_A
#define AU_SAI          SAI1
#define AU_SAI_A        SAI1_Block_A
#define AU_SAI_B        SAI1_Block_B
#define AU_SAI_RccEn()  RCC->APB2ENR |= RCC_APB2ENR_SAI1EN
#define AU_SAI_RccDis() RCC->APB2ENR &= ~RCC_APB2ENR_SAI1EN

// LED
#define LED_R_PIN       { GPIOD, 13, TIM4, 2, invNotInverted, omPushPull, 255 }
#define LED_B_PIN       { GPIOD, 14, TIM4, 3, invNotInverted, omPushPull, 255 }
#define LED_G_PIN       { GPIOD, 15, TIM4, 4, invNotInverted, omPushPull, 255 }

// Acc
#define ACG_IRQ_PIN     GPIOB, 0
#define ACG_PWR_PIN     GPIOE, 15

// Radio: SPI, PGpio, Sck, Miso, Mosi, Cs, Gdo0
#define CC_Setup0       SPI2, GPIOB, 13,14,15, GPIOB,12, GPIOB,1

#define DBG_PIN         GPIOB, 8

// I2C
#define I2C1_GPIO       GPIOB
#define I2C1_SCL        6
#define I2C1_SDA        7
#define I2C2_GPIO       GPIOB
#define I2C2_SCL        10
#define I2C2_SDA        11
#define I2C3_GPIO       GPIOC
#define I2C3_SCL        0
#define I2C3_SDA        1
// I2C Alternate Function
#define I2C_AF          AF4

#endif // GPIO

#if 1 // =========================== I2C =======================================
// i2cclkPCLK1, i2cclkSYSCLK, i2cclkHSI
#define I2C_CLK_SRC     i2cclkHSI
#define I2C_BAUDRATE_HZ 400000
#endif

#if ADC_REQUIRED // ======================= Inner ADC ==========================
// Clock divider: clock is generated from the APB2
#define ADC_CLK_DIVIDER		adcDiv2

// ADC channels
#define ADC_BATTERY_CHNL 	14
// ADC_VREFINT_CHNL
#define ADC_CHANNELS        { ADC_BATTERY_CHNL, ADC_VREFINT_CHNL }
#define ADC_CHANNEL_CNT     2   // Do not use countof(AdcChannels) as preprocessor does not know what is countof => cannot check
#define ADC_SAMPLE_TIME     ast24d5Cycles
#define ADC_OVERSAMPLING_RATIO  64   // 1 (no oversampling), 2, 4, 8, 16, 32, 64, 128, 256
#endif

#if 1 // =========================== DMA =======================================
// ==== Uart ====
// Remap is made automatically if required
#define UART_DMA_TX     STM32_DMA_STREAM_ID(2, 6)
#define UART_DMA_RX     STM32_DMA_STREAM_ID(2, 7)
#define UART_DMA_CHNL   2
#define UART_DMA_TX_MODE(Chnl) (STM32_DMA_CR_CHSEL(Chnl) | DMA_PRIORITY_LOW | STM32_DMA_CR_MSIZE_BYTE | STM32_DMA_CR_PSIZE_BYTE | STM32_DMA_CR_MINC | STM32_DMA_CR_DIR_M2P | STM32_DMA_CR_TCIE)
#define UART_DMA_RX_MODE(Chnl) (STM32_DMA_CR_CHSEL(Chnl) | DMA_PRIORITY_MEDIUM | STM32_DMA_CR_MSIZE_BYTE | STM32_DMA_CR_PSIZE_BYTE | STM32_DMA_CR_MINC | STM32_DMA_CR_DIR_P2M | STM32_DMA_CR_CIRC)

// ESP UARTs
#define UART2_DMA_TX     STM32_DMA_STREAM_ID(1, 7)
#define UART2_DMA_RX     STM32_DMA_STREAM_ID(1, 6)
#define UART3_DMA_TX     STM32_DMA_STREAM_ID(1, 2)
#define UART3_DMA_RX     STM32_DMA_STREAM_ID(1, 3)

// ==== SAI ====
#define SAI_DMA_A       STM32_DMA_STREAM_ID(2, 1)
#define SAI_DMA_CHNL    1

// ==== SDMMC ====
#define STM32_SDC_SDMMC1_DMA_STREAM   STM32_DMA_STREAM_ID(2, 5)


// ==== I2C ====
#define I2C1_DMA_TX     STM32_DMA_STREAM_ID(1, 6)
#define I2C1_DMA_RX     STM32_DMA_STREAM_ID(1, 7)
#define I2C1_DMA_CHNL   3
#define I2C2_DMA_TX     STM32_DMA_STREAM_ID(1, 4)
#define I2C2_DMA_RX     STM32_DMA_STREAM_ID(1, 5)
#define I2C2_DMA_CHNL   3
#define I2C3_DMA_TX     STM32_DMA_STREAM_ID(1, 2)
#define I2C3_DMA_RX     STM32_DMA_STREAM_ID(1, 3)
#define I2C3_DMA_CHNL   3

#if ADC_REQUIRED
#define ADC_DMA         STM32_DMA1_STREAM1
#define ADC_DMA_MODE    STM32_DMA_CR_CHSEL(0) |   /* DMA1 Stream1 Channel0 */ \
                        DMA_PRIORITY_LOW | \
                        STM32_DMA_CR_MSIZE_HWORD | \
                        STM32_DMA_CR_PSIZE_HWORD | \
                        STM32_DMA_CR_MINC |       /* Memory pointer increase */ \
                        STM32_DMA_CR_DIR_P2M |    /* Direction is peripheral to memory */ \
                        STM32_DMA_CR_TCIE         /* Enable Transmission Complete IRQ */
#endif // ADC

#endif // DMA

#if 1 // ========================== USART ======================================
#define PRINTF_FLOAT_EN TRUE
#define UART_TXBUF_SZ   4096
#define UART_RXBUF_SZ   256
#define CMD_BUF_SZ      256

#define CMD_UART        USART1
#define ESP_BOOT_UART   USART2
#define ESP_CMD_UART    USART3

#define CMD_UART_PARAMS \
    CMD_UART, UART_TX_PIN, UART_RX_PIN, \
    UART_DMA_TX, UART_DMA_RX, UART_DMA_TX_MODE(UART_DMA_CHNL), UART_DMA_RX_MODE(UART_DMA_CHNL), \
    uartclkHSI // Use independent clock

#define ESP_UART_PARAMS \
    ESP_CMD_UART, ESP_RX2_MCU_TX, ESP_TX2_MCU_RX, \
    UART3_DMA_TX, UART3_DMA_RX, UART_DMA_TX_MODE(UART_DMA_CHNL), UART_DMA_RX_MODE(UART_DMA_CHNL), \
    uartclkHSI // Use independent clock

#endif

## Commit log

2022-05-10 Sch done, layout in progress
2022-05-12 Placement in progress
2022-05-14 Main PCB sent to factory
2022-05-14 + ANT PCB
2022-05-15 Minor
2022-05-17 Uart CMD works
2022-05-20 Discover, StopDiscover works
2022-05-21 Connects
2022-05-22 + STM32 prj Addr found
2022-05-24 + SAI sample rate setting is ok
2022-05-26 Before switch to: ESP is I2S master, SAI is i2s slave
2022-05-29 "I am alive" played by BT. Not reliable, though
